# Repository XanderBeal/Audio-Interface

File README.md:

# Audio-Interface

Using the PCM2903 audio interface IC from TI
-  Analog dual channel audio to USB and dual channel output
    - Configured for single channel guitar input and single channel headphone output

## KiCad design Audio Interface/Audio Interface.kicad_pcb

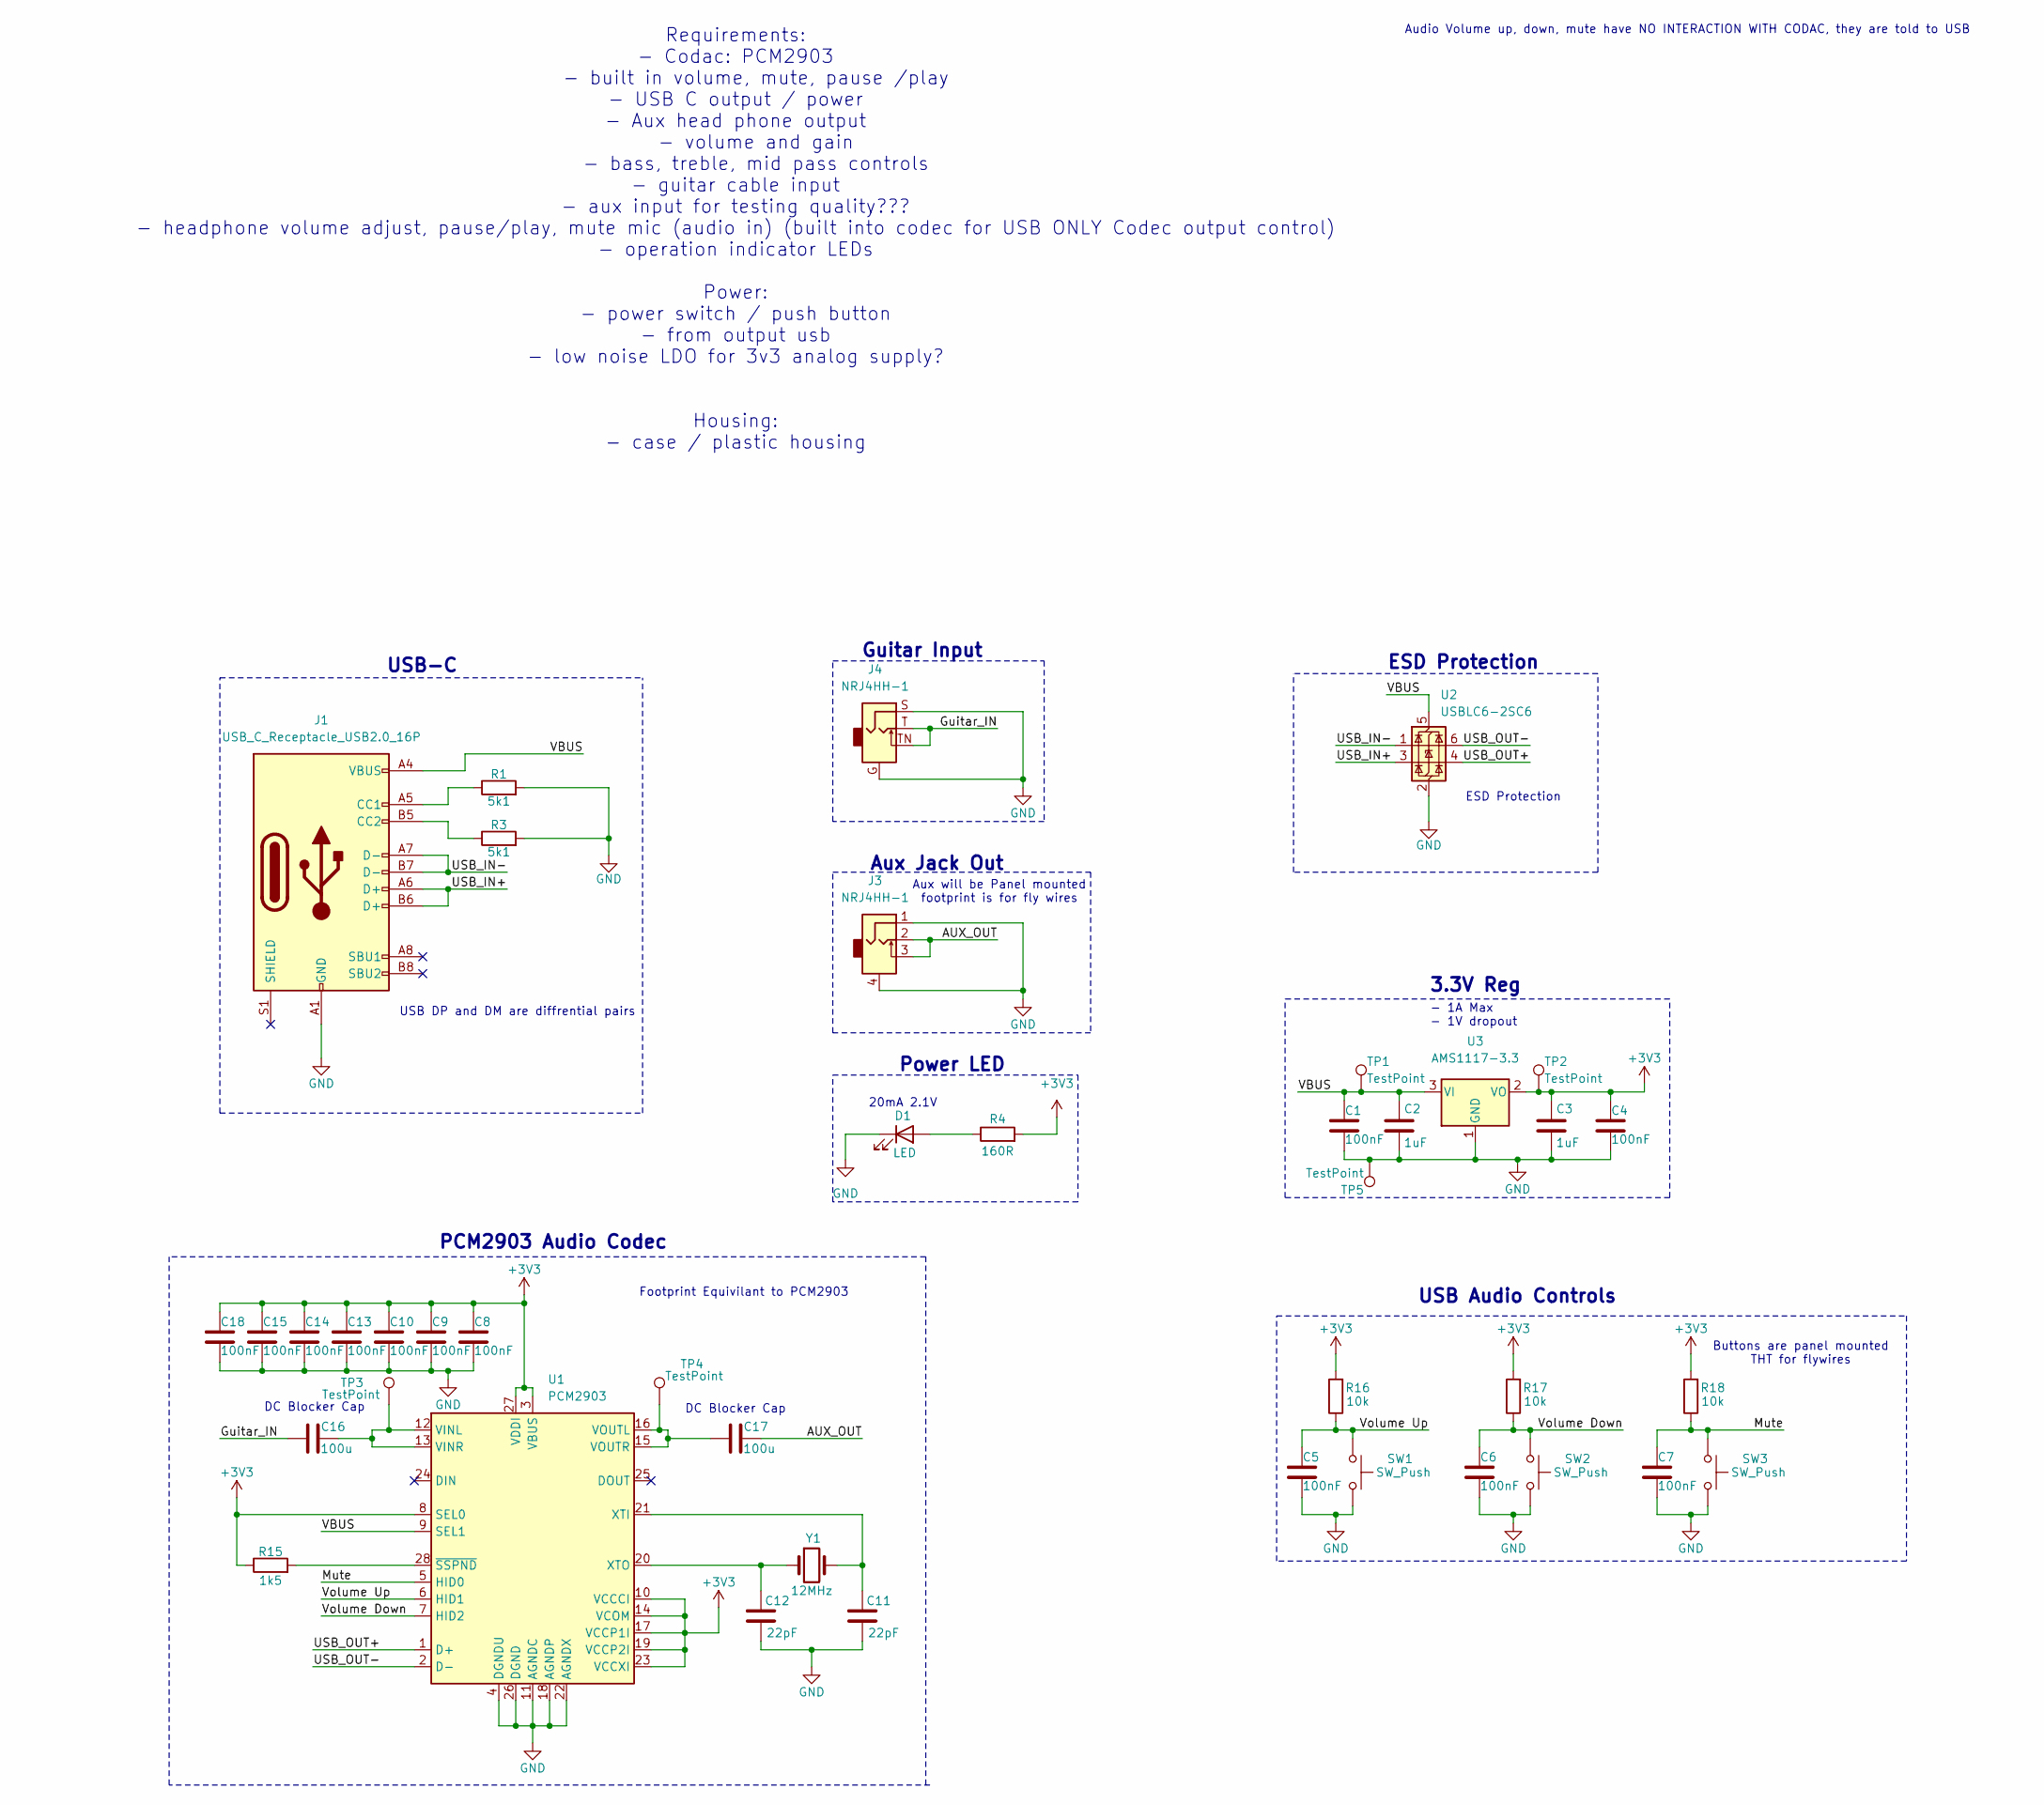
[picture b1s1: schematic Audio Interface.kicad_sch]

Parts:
C1, C4, C5, C6, C7, C8, C9, C10, C13, C14, C15, C18: 100nF; C_0402_1005Metric_Pad0.74x0.62mm_HandSolder
C2, C3: 1uF; C_0402_1005Metric_Pad0.74x0.62mm_HandSolder
C11, C12: 22pF; C_0402_1005Metric_Pad0.74x0.62mm_HandSolder
C16, C17: 100u; CP_Elec_6.3x7.7
D1: LED; LED_D4.0mm
J1: USB_C_Receptacle_USB2.0_16P; USB_C_Receptacle_G-Switch_GT-USB-7010ASV
J3: NRJ4HH-1; PinHeader_1x04_P2.54mm_Vertical
J4: NRJ4HH-1; Jack_6.35mm_Neutrik_NRJ4HH-1_Horizontal
R1, R3: 5k1; R_0402_1005Metric_Pad0.72x0.64mm_HandSolder
R4: 160R; R_0402_1005Metric_Pad0.72x0.64mm_HandSolder
R15: 1k5; R_0402_1005Metric_Pad0.72x0.64mm_HandSolder
R16, R17, R18: 10k; R_0603_1608Metric_Pad0.98x0.95mm_HandSolder
SW1, SW2, SW3: SW_Push; R_Axial_DIN0204_L3.6mm_D1.6mm_P2.54mm_Vertical
TP1, TP2, TP3, TP4, TP5: TestPoint; TestPoint_Pad_D1.0mm
U1: PCM2903; SSOP-28_5.3x10.2mm_P0.65mm
U2: USBLC6-2SC6; SOT-23-6
U3: AMS1117-3.3; SOT-89-3
Y1: 12MHz; Crystal_SMD_3225-4Pin_3.2x2.5mm_HandSoldering

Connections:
+3V3: C3.1, C4.1, C8.1, C9.1, C10.1, C13.1, C14.1, C15.1, C18.1, R4.2, R15.1, R16.2, R17.2, R18.2, TP2.1, U1.3 (VBUS), U1.8 (SEL0), U1.10 (VCCCI), U1.14 (VCOM), U1.17 (VCCP1I), U1.19 (VCCP2I), U1.23 (VCCXI), U1.27 (VDDI), U3.2 (VO)
/AUX_OUT: C17.2, J3.2, J3.3
/Guitar_IN: C16.1, J4.T, J4.TN
/Mute: C7.1, R18.1, SW3.1, U1.5 (HID0)
/USB_IN+: J1.A6 (D+), J1.B6 (D+), U2.3 (I/O2)
/USB_IN-: J1.A7 (D-), J1.B7 (D-), U2.1 (I/O1)
/USB_OUT+: U1.1 (D+), U2.4 (I/O2)
/USB_OUT-: U1.2 (D-), U2.6 (I/O1)
/VBUS: C1.1, C2.1, J1.A4 (VBUS), J1.A9 (VBUS), J1.B4 (VBUS), J1.B9 (VBUS), TP1.1, U1.9 (SEL1), U2.5 (VBUS), U3.3 (VI)
/Volume Down: C6.1, R17.1, SW2.1, U1.7 (HID2)
/Volume Up: C5.1, R16.1, SW1.1, U1.6 (HID1)
GND: C1.2, C2.2, C3.2, C4.2, C5.2, C6.2, C7.2, C8.2, C9.2, C10.2, C11.2, C12.2, C13.2, C14.2, C15.2, C18.2, D1.1 (K), J1.A1 (GND), J1.A12 (GND), J1.B1 (GND), J1.B12 (GND), J3.1, J3.4, J4.G, J4.S, R1.2, R3.2, SW1.2, SW2.2, SW3.2, TP5.1, U1.4 (DGNDU), U1.11 (AGNDC), U1.18 (AGNDP), U1.22 (AGNDX), U1.26 (DGND), U2.2 (GND), U3.1 (GND)
unnamed: D1.2 (A), R4.1
unnamed: J1.A5 (CC1), R1.1
unnamed: J1.B5 (CC2), R3.1
unnamed: C16.2, TP3.1, U1.12 (VINL), U1.13 (VINR)
unnamed: C17.1, TP4.1, U1.15 (VOUTR), U1.16 (VOUTL)
unnamed: C11.1, U1.21 (XTI), Y1.2
unnamed: C12.1, U1.20 (XTO), Y1.1
unnamed: R15.2, U1.28 (~SSPND)

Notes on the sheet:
ESD Protection
DC Blocker Cap
PCM2903 Audio Codec
Power LED
USB DP and DM are diffrential pairs
Guitar Input
3.3V Reg
Audio Volume up, down, mute have NO INTERACTION WITH CODAC, they are told to USB
- 1A Max - 1V dropout
Buttons are panel mounted THT for flywires
USB Audio Controls
USB-C
Aux will be Panel mounted footprint is for fly wires
Footprint Equivilant to PCM2903
Aux Jack Out
20mA 2.1V
Requirements: - Codac: PCM2903 - built in volume, mute, pause /play - USB C output / power - Aux head phone output - volume and gain - bass, treble, mid pass controls - guitar cable input - aux input for testing quality??? - headphone volume adjust, pause/play, mute mic (audio in) (built into codec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

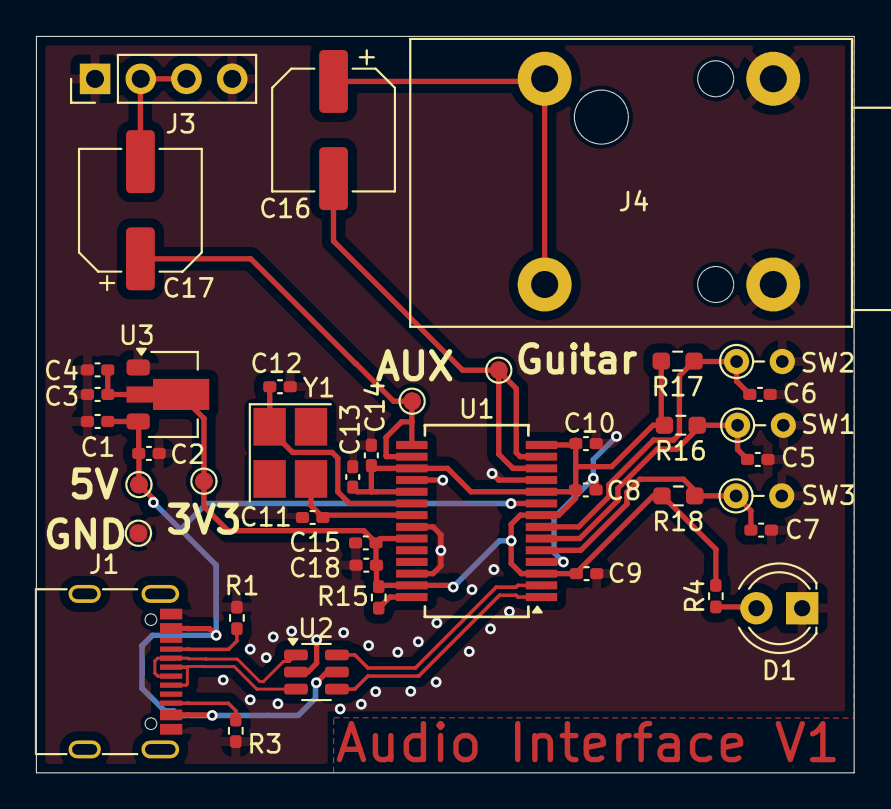
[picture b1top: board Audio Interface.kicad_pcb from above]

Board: 2 copper layers, 45.4 x 40.9 mm, 41 parts (0 on the bottom side), 20 nets.

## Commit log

2024-07-25 KiCad Files Initial Commit
2024-07-25 commit 2 of kicad files test
2024-08-08 ordered board
